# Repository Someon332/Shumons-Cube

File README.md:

# Shumons-Cube
My take on hackpad!

# CAD

Two seperately printed case parts (top and bottom) and the actual PCB. 
It's very basic but I can always swap out the case lol. The PCB is pretty basic too, just the switches and 4 neopixels, but it's more than enough for my purposes (hotkeys). 

# PCB
Schematic: 

PCB: 

Not too complicated, had to use some vias because of all the criss-crossing connections. 

# Firmware
QMK! 

# BOM
1x Case

1x Seeed XIAO RP2040 (THT)

10x Cherry-MX Switches

4x SK6812 MINI-E LEDs

10x DSA Keycaps

4x M3x16mm Screws

----------

# IRL Photo and Demo

YT Video Link: https://youtube.com/shorts/_0YjuRMz1Ag

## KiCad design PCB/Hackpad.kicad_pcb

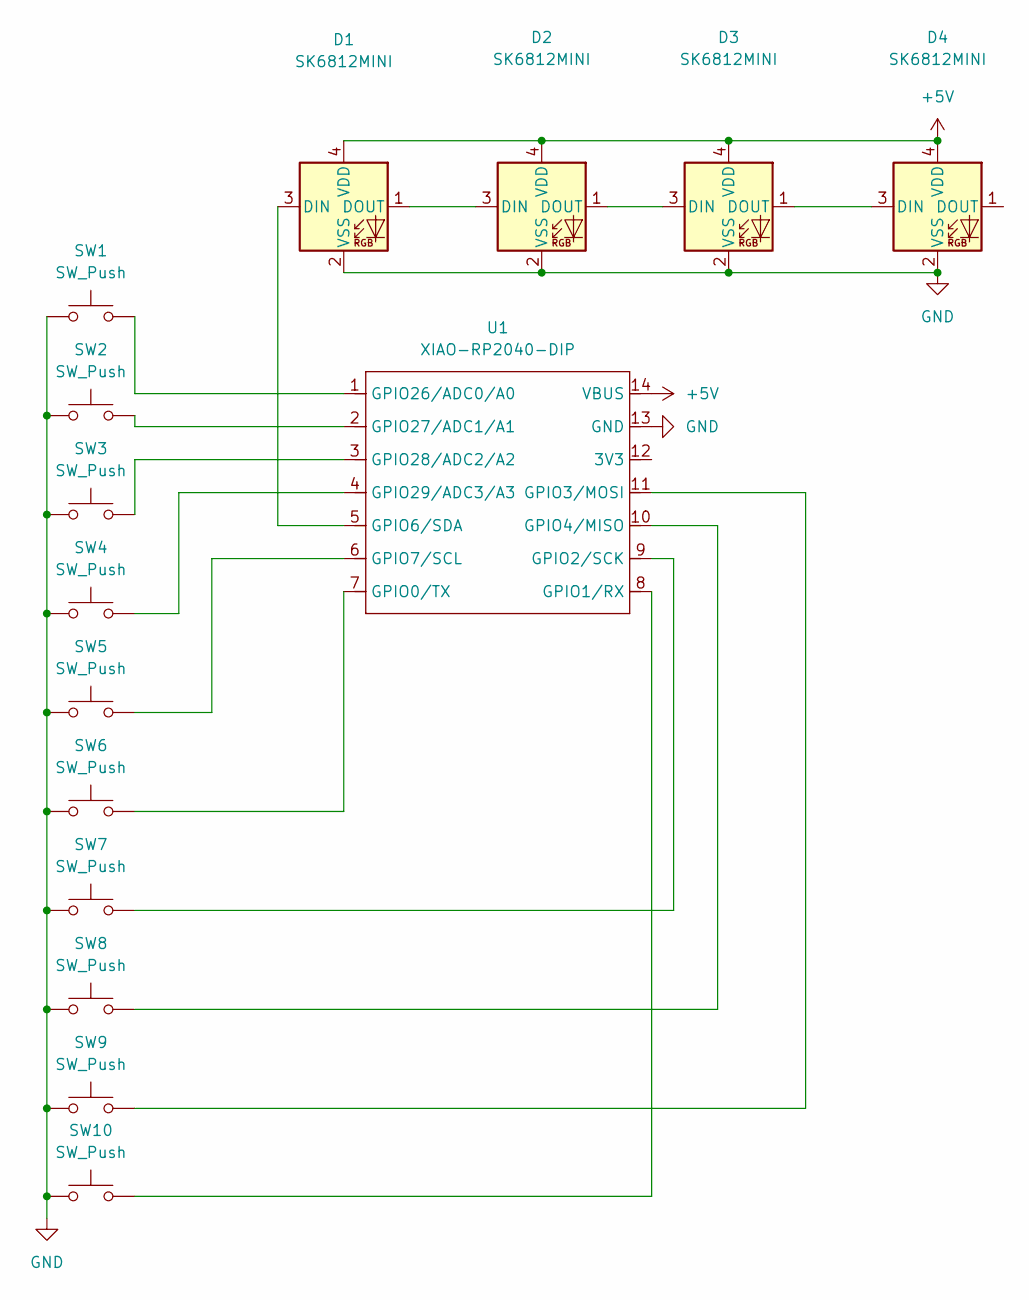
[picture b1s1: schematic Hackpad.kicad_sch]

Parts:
D1, D2, D3, D4: SK6812MINI; LED_SK6812MINI_PLCC4_3.5x3.5mm_P1.75mm
SW1, SW2, SW3, SW4, SW5, SW6, SW7, SW8, SW9, SW10: SW_Push; SW_Cherry_MX_1.00u_PCB
U1: XIAO-RP2040-DIP

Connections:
+5V: D1.4 (VDD), D2.4 (VDD), D3.4 (VDD), D4.4 (VDD), U1.14 (VBUS)
GND: D1.2 (VSS), D2.2 (VSS), D3.2 (VSS), D4.2 (VSS), SW1.1, SW2.1, SW3.1, SW4.1, SW5.1, SW6.1, SW7.1, SW8.1, SW9.1, SW10.1, U1.13 (GND)
unnamed: D1.3 (DIN), U1.5 (GPIO6/SDA)
unnamed: D1.1 (DOUT), D2.3 (DIN)
unnamed: D2.1 (DOUT), D3.3 (DIN)
unnamed: D3.1 (DOUT), D4.3 (DIN)
unnamed: SW6.2, U1.7 (GPIO0/TX)
unnamed: SW10.2, U1.8 (GPIO1/RX)
unnamed: SW7.2, U1.9 (GPIO2/SCK)
unnamed: SW9.2, U1.11 (GPIO3/MOSI)
unnamed: SW8.2, U1.10 (GPIO4/MISO)
unnamed: SW5.2, U1.6 (GPIO7/SCL)
unnamed: SW1.2, U1.1 (GPIO26/ADC0/A0)
unnamed: SW2.2, U1.2 (GPIO27/ADC1/A1)
unnamed: SW3.2, U1.3 (GPIO28/ADC2/A2)
unnamed: SW4.2, U1.4 (GPIO29/ADC3/A3)

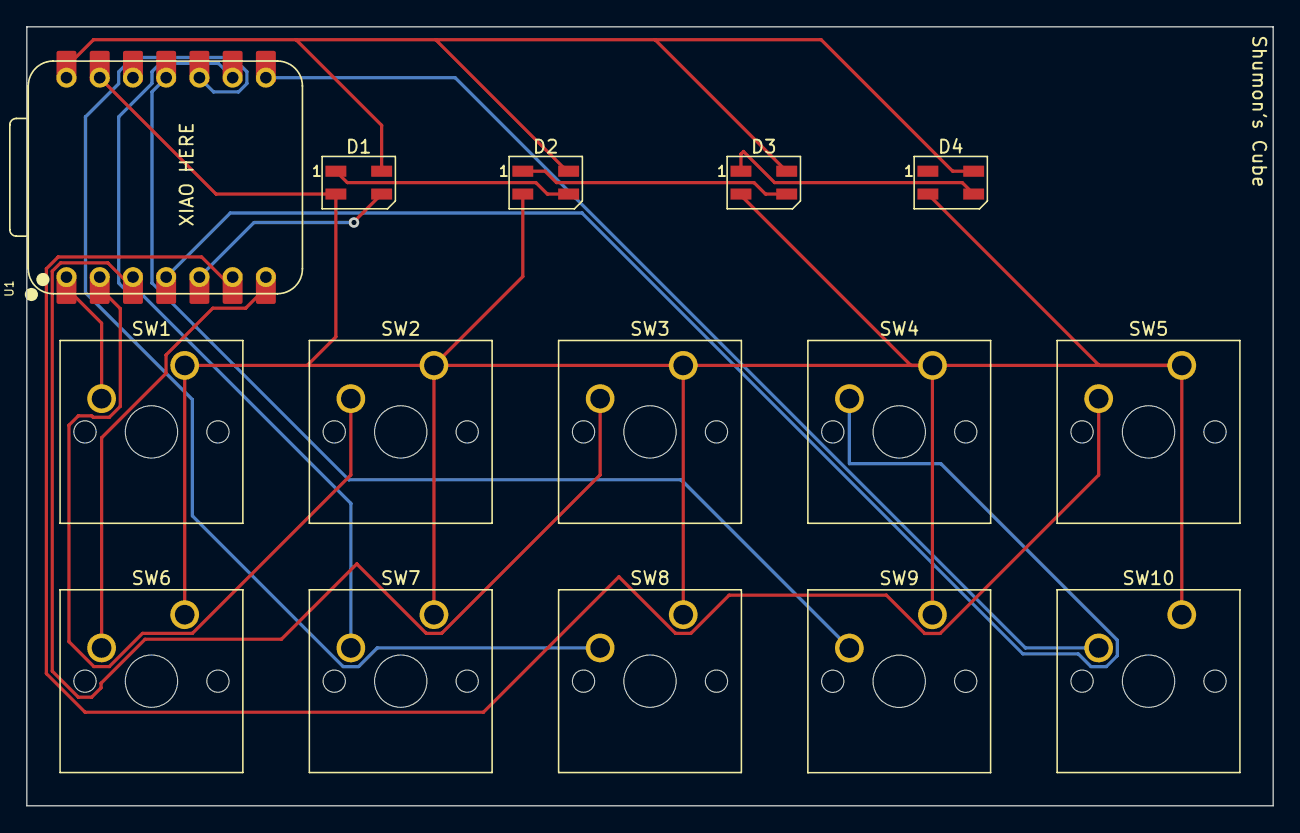
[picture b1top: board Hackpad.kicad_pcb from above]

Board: 2 copper layers, 95.2 x 59.5 mm, 15 parts (0 on the bottom side), 16 nets.

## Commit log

2025-06-17 Create temp
2025-06-18 Rename Hackpad Assembled v1.3mf to CAD/Hackpad Assembled v1.3mf
2025-06-18 Rename Hackpad.kicad_pro to PCB/Hackpad.kicad_pro
2025-06-18 Rename Gerbers.zip.zip to Production/Gerbers.zip
